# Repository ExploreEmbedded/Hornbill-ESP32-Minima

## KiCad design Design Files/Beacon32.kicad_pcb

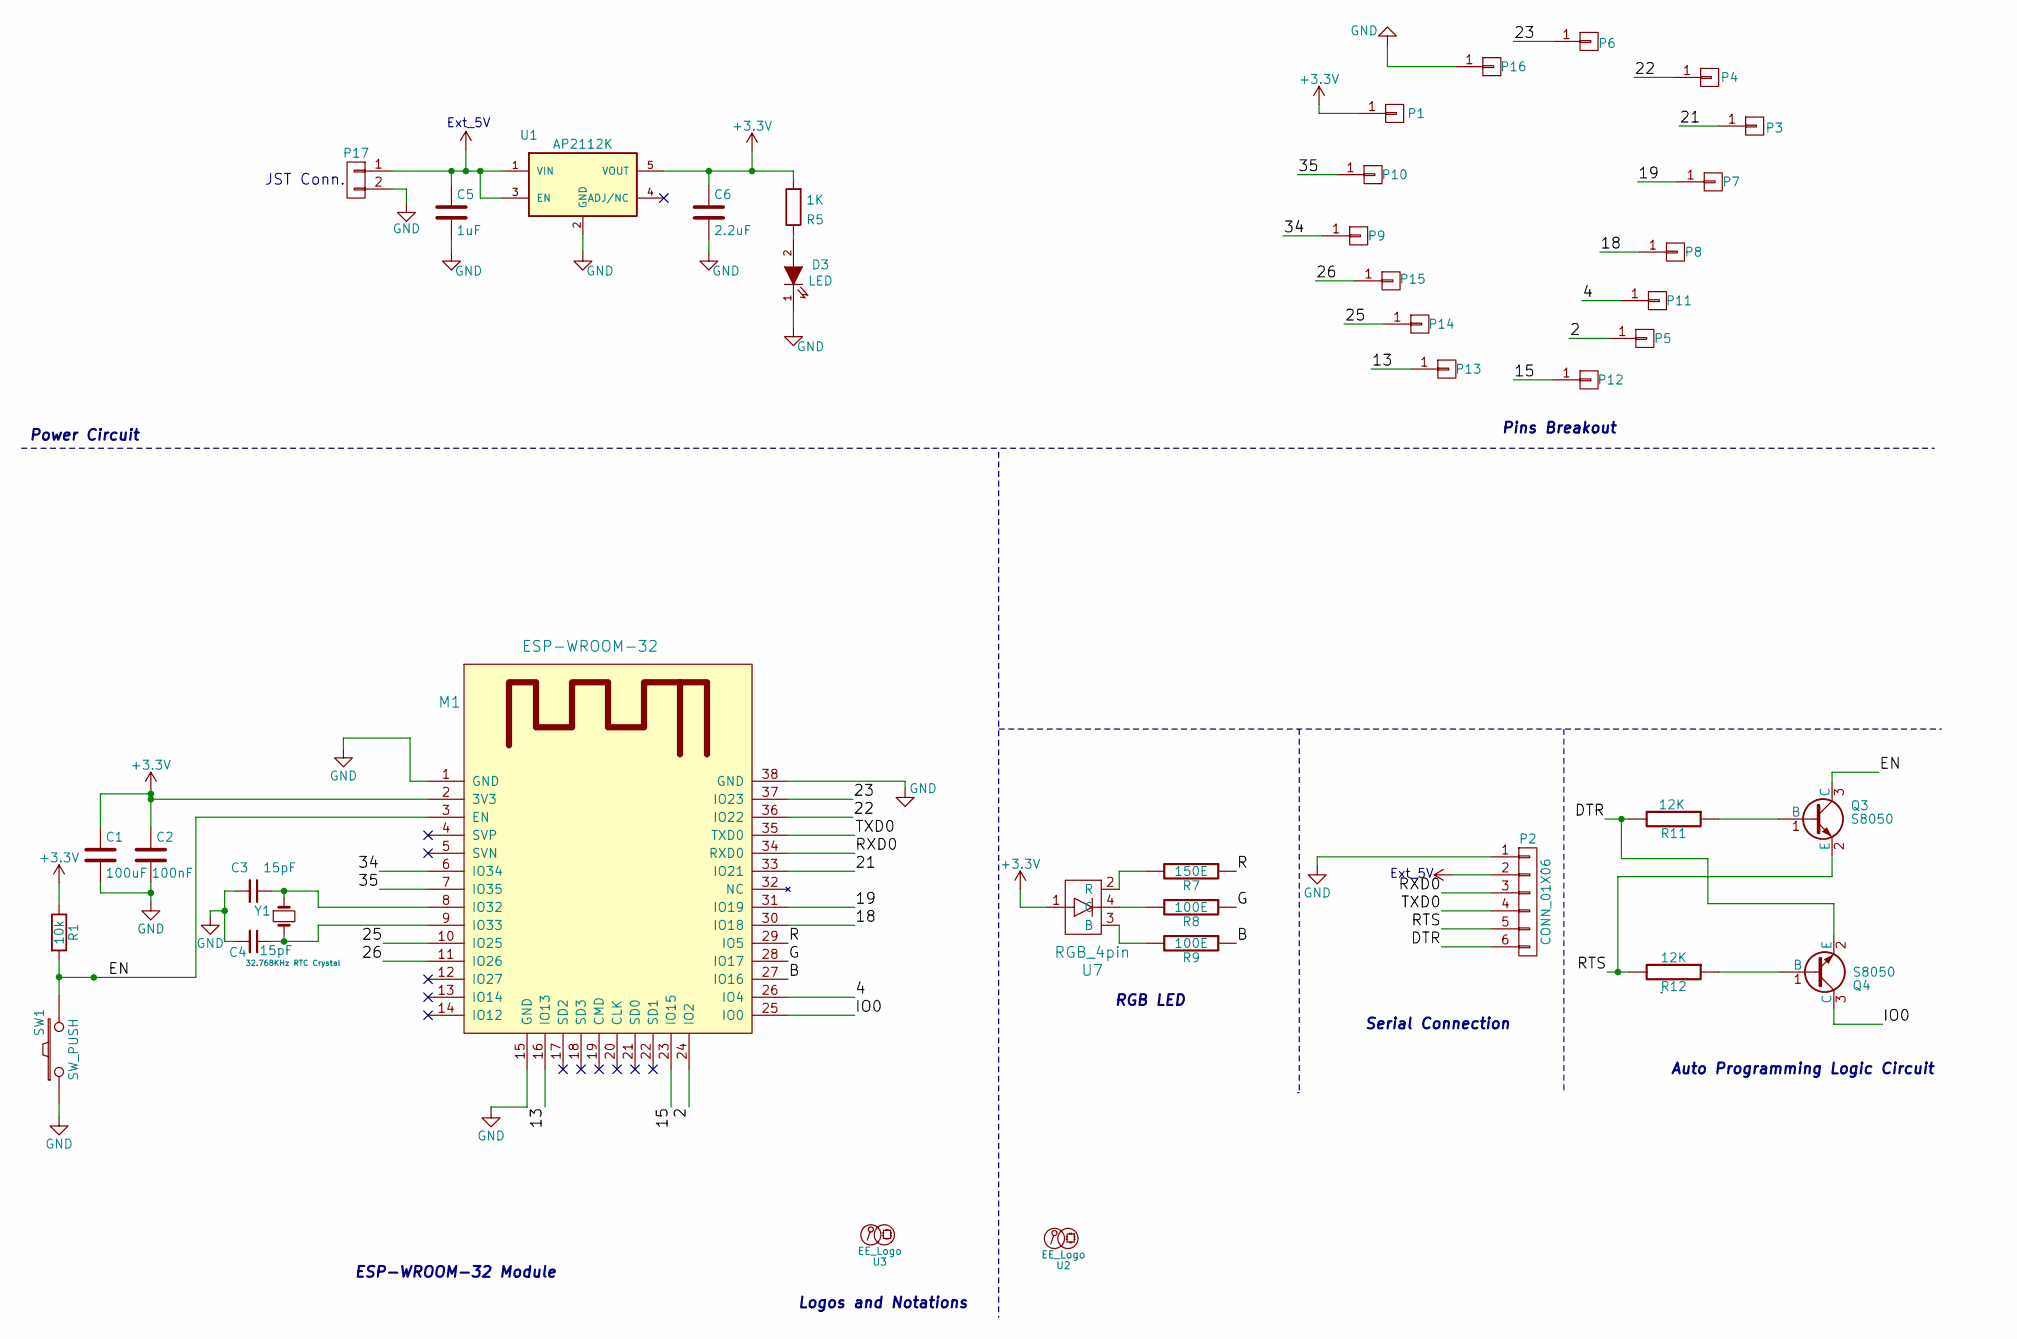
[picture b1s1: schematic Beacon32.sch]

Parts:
C1: 100uF; C_1206
C2: 100nF; C_0603
C3, C4: 15pF; C_0603
C5: 1uF; C_0603
C6: 2.2uF; C_0603
D3: LED; LED-0603
M1: ESP-WROOM-32; ESP-32S
P1, P3, P4, P5, P6, P7, P8, P9, P10, P11, P12, P13, P14, P15, P16: CONN_01X01; MinimaPad_3.5mm
P2: CONN_01X06; 1X06
P17: CONN_01X02; s2b-ph-sm4-tb
Q3, Q4: S8050; SOT-23
R1: 10k; R_0603
R5: 1K; R_0603
R7: 150E; R_0603
R8, R9: 100E; R_0603
R11, R12: 12K; R_0603
SW1: SW_PUSH; smd_push2_New
U1: AP2112K; SOT-23-5
U2: EE_Logo; Hornbill_ESP32_minima
U3: EE_Logo; Logo_8
U7: RGB_4pin; RGB_SMD_4pin_New
Y1: 32.768KHz RTC Crystal; SMD_RTC_Crstl

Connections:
+3V3: C1.1, C2.1, C6.1, M1.2 (3V3), P1.1, R1.1, R5.2, U1.5 (VOUT), U7.1
+5V: C5.1, P2.2, P17.1, U1.1 (VIN), U1.3 (EN)
/2: M1.24 (IO2), P5.1
/4: M1.26 (IO4), P11.1
/13: M1.16 (IO13), P13.1
/15: M1.23 (IO15), P12.1
/18: M1.30 (IO18), P8.1
/19: M1.31 (IO19), P7.1
/21: M1.33 (IO21), P3.1
/22: M1.36 (IO22), P4.1
/23: M1.37 (IO23), P6.1
/25: M1.10 (IO25), P14.1
/26: M1.11 (IO26), P15.1
/34: M1.6 (IO34), P9.1
/35: M1.7 (IO35), P10.1
/B: M1.27 (IO16), R9.1
/DTR: P2.6, Q4.2 (E), R11.2
/EN: M1.3 (EN), Q3.3 (C), R1.2, SW1.2
/G: M1.28 (IO17), R8.1
/IO0: M1.25 (IO0), Q4.3 (C)
/R: M1.29 (IO5), R7.1
/RTS: P2.5, Q3.2 (E), R12.2
/RXD0: M1.34 (RXD0), P2.3
/TXD0: M1.35 (TXD0), P2.4
GND: C1.2, C2.2, C3.2, C4.2, C5.2, C6.2, D3.1 (K), M1.1 (GND), M1.15 (GND), M1.38 (GND), P2.1, P16.1, P17.2, SW1.1, U1.2 (GND)
unnamed: C3.1, M1.8 (IO32), Y1.1
unnamed: C4.1, M1.9 (IO33), Y1.2
unnamed: D3.2 (A), R5.1
unnamed: Q3.1 (B), R11.1
unnamed: Q4.1 (B), R12.1
unnamed: R7.2, U7.2 (R)
unnamed: R8.2, U7.4 (G)
unnamed: R9.2, U7.3 (B)

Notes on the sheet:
RGB LED
Logos and Notations
Pins Breakout
Power Circuit
Auto Programming Logic Circuit
ESP-WROOM-32 Module
Ext_5V
Serial Connection
JST Conn.

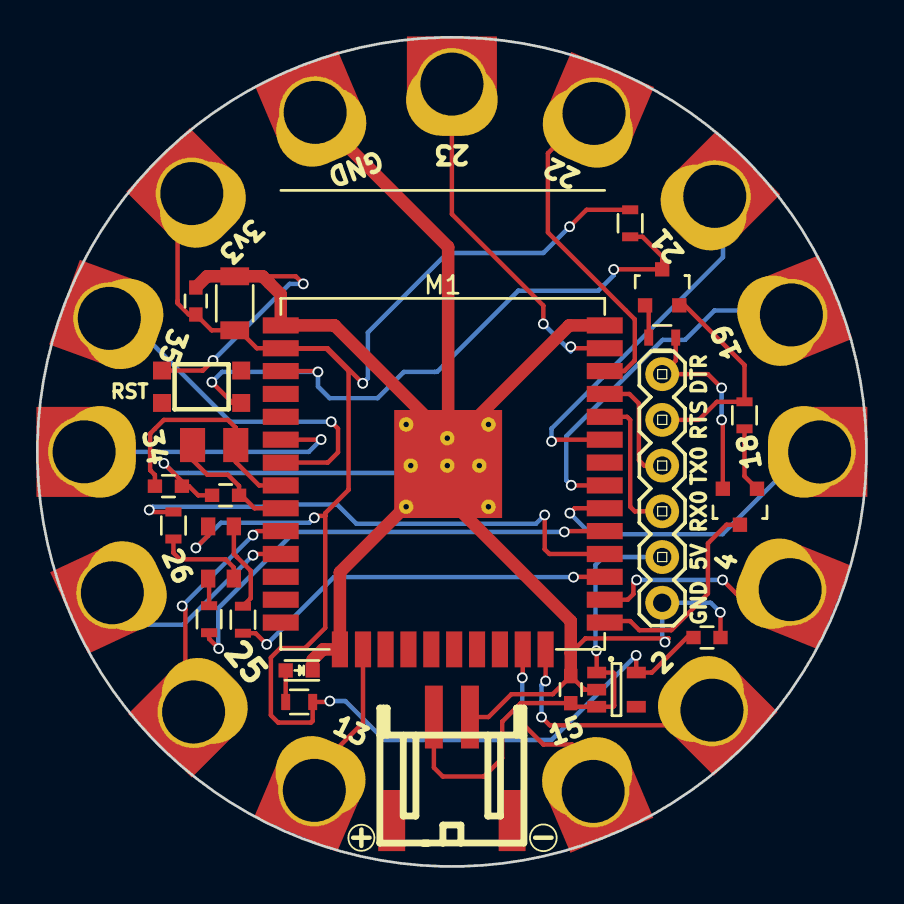
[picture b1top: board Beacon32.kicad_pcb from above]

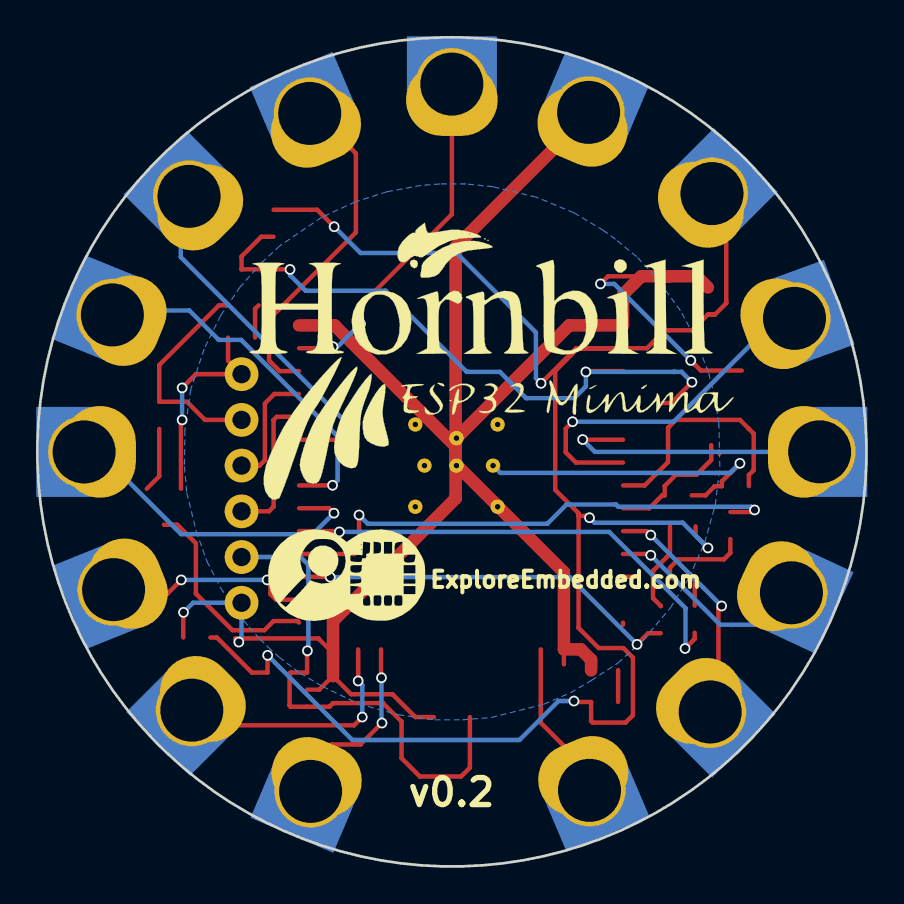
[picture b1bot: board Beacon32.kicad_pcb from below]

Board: 2 copper layers, 46.1 x 46.1 mm, 40 parts (2 on the bottom side), 33 nets.

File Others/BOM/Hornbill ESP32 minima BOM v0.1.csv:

Id,Designator,Package,Quantity,Designation,Supplier and ref,,,,
1,M1,ESP-32S,1,ESP-WROOM-32,,,,,
2,P2,1X06,1,CONN_01X06,,,,,
3,C1,C_1206,1,100uF,,,,,
4,C2,C_0603,1,100nF,,,,,
5,"C3,C4",C_0603,2,15pF,,,,P15,"P16"";""Specialpad"";15;""CONN_01X01"";;;"
6,C5,C_0603,1,1uF,,,,,
7,C6,C_0603,1,2.2uF,,,,,
8,D3,LED-0603,1,LED,,,,,
9,"Q3,Q4",SOT-23,2,S8050,,,,,
10,R1,R_0603,1,10K,,,,,
11,R5,R_0603,1,1K,,,,,
12,R7,R_0603,1,150E,,,,,
13,"R8,R9",R_0603,2,100E,,,,,
14,"R11,R12",R_0603,2,12K,,,,,
15,U1,SOT-23-5,1,AP2112K,,,,,
16,U3,Logo_8,1,EE_Logo,,,,,
17,U7,sfh5712,1,RGB_4pin,,,,,
18,Y1,SMD_RTC_Crstl,1,32.768KHz RTC Crystal,,,,,
19,P17,s2b-ph-sm4-tb,1,CONN_01X02,,,,,
20,"P1,P3,P4,P5,P6,P7,P8,P9,P10,P11,P12,P13,P14,P15,P16",Specialpad,15,CONN_01X01,,,,,
21,U2,Hornbill_ESP32_minima,1,EE_Logo,,,,,

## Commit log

2017-04-22 Added Design Files
2017-04-22 BOM generated
2017-04-27 Issue closed
    Added Reset switch and RGB footprint changed
2017-04-27 Gerber file genereted
2017-05-01 Drill Size Increased
2017-05-02 Resized pads to 3.5mm
2017-05-02 Gerber file generated for v0.2
2017-06-07 Process sheet added
2017-06-08 Process sheet modified
